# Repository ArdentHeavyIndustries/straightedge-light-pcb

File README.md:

# straightedge-light-pcb
Design files for the the custom circuit board that holds Straightedge's LEDs.

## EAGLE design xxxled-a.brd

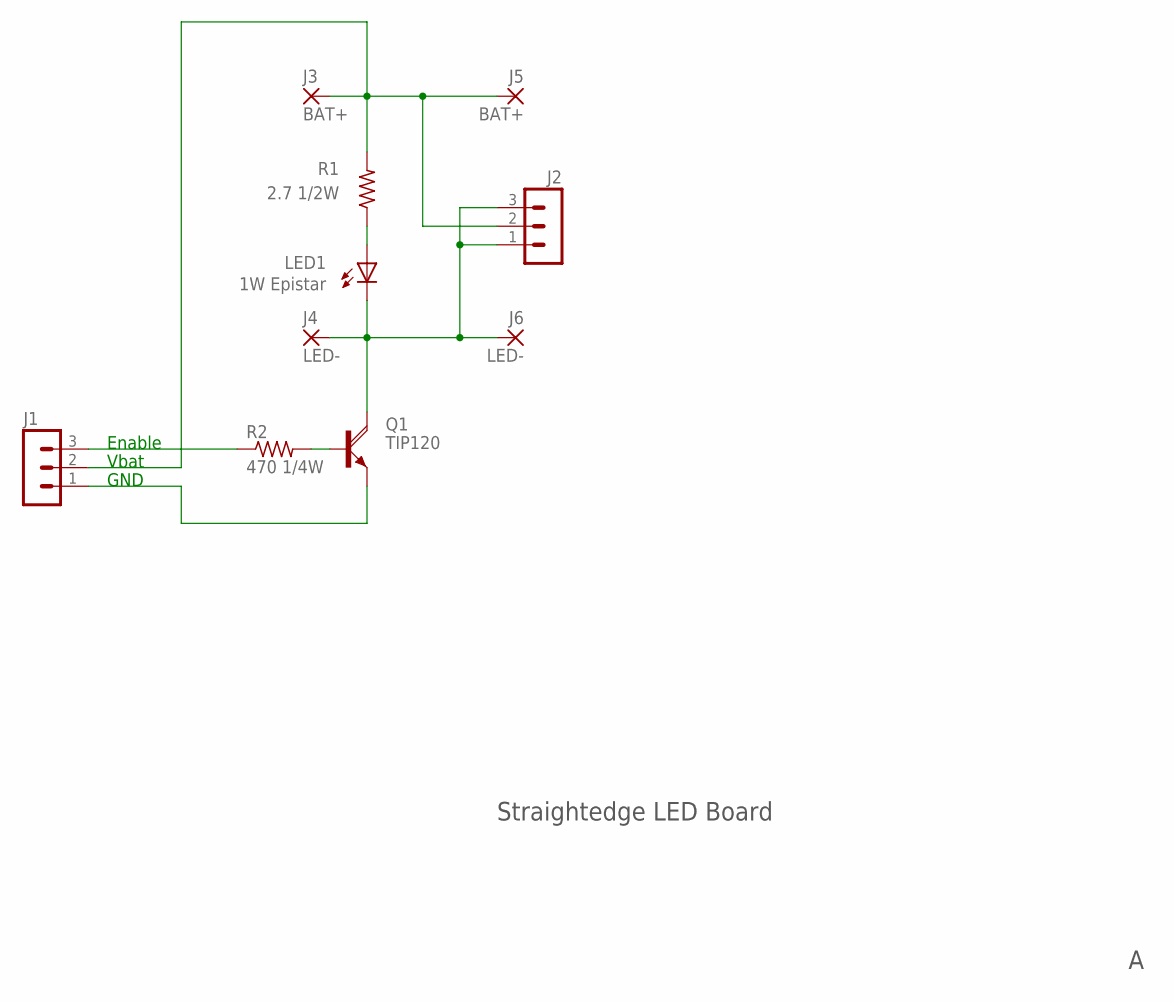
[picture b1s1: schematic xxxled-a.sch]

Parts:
J1, J2: MA03-1
J3, J5: BAT+; 2,54/1,1
J4, J6: LED-; 2,54/1,1
LED1: 1W Epistar; POWER_LED_EDGE
Q1: TIP120; TO220AH
R1: 2.7 1/2W; 0309/12
R2: 470 1/4W; 0207/10

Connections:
unnamed: J1.3, R2.1
unnamed: Q1.B, R2.2
unnamed: J2.1, J2.3, J4.1, J6.1, LED1.P$C (C), Q1.C
unnamed: LED1.P$A (A), R1.1
unnamed: J1.2, J2.2, J3.1, J5.1, R1.2
unnamed: J1.1, Q1.E

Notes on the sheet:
Straightedge LED Board
Vbat
GND
Enable

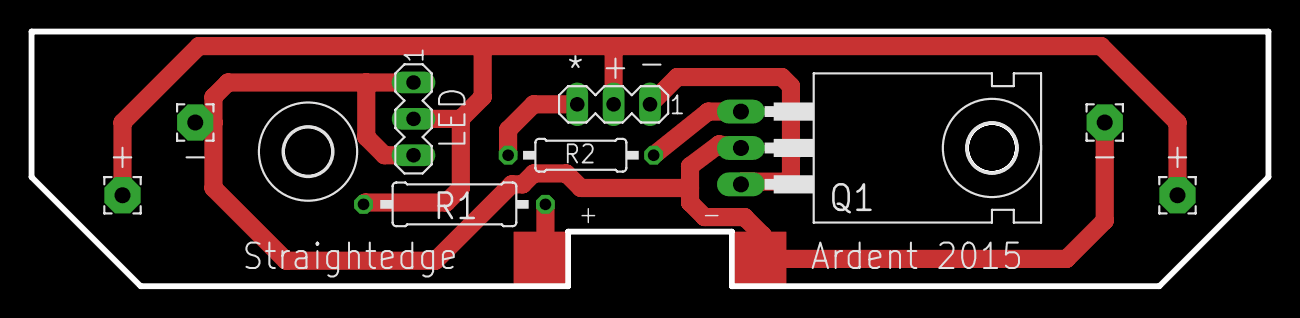
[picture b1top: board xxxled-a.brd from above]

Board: 2 copper layers, 86.4 x 17.8 mm, 12 parts (0 on the bottom side), 6 nets.

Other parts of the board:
U$1, U$2: 3,3

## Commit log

2015-07-23 Add .DS_Store
2015-07-23 Initial schematic
2015-07-23 First draft single-sided PCB layout
2015-07-24 * added J2 to connect the two board clusters on one stake to each other * Tidied silkscreen layout * Moved mounting holes (and Q1) in a bit * Layout with all 50mil traces * Down to 1/2W for R1, still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
2015-07-24 Generated manufacturing and doc files
2015-07-24 Slightly nicer image
2015-07-24 Add the render to README
2015-07-26 Switch to 2.7 ohm power resistor
    With the prototype PCB and 4 LEDs, this gives a peak current of ~0.75 A at 4.5V
